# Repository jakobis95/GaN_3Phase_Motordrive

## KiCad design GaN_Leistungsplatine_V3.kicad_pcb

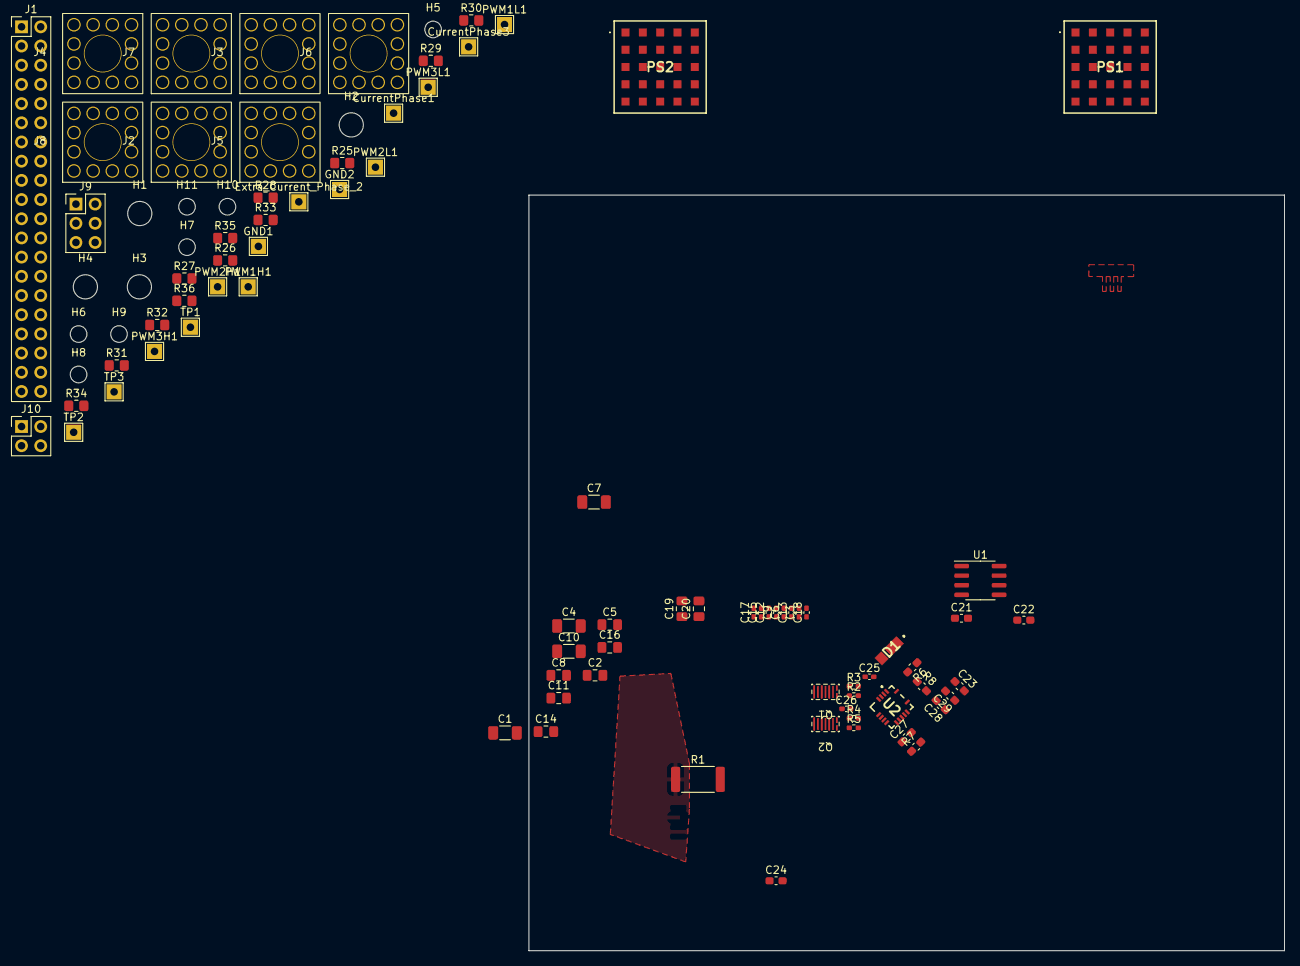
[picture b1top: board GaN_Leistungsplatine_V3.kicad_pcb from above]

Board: 4 copper layers, 100.0 x 100.0 mm, 91 parts (0 on the bottom side), 45 nets, no tracks yet.

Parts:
C1, C4, C7, C10: 4.7u; C_1206_3216Metric_Pad1.33x1.80mm_HandSolder
C2, C5, C8, C11, C14, C16, C19, C20: 1u; C_0805_2012Metric_Pad1.18x1.45mm_HandSolder
C3, C6, C9, C12, C13, C15, C17, C18: 0.1u; C_0402_1005Metric_Pad0.74x0.62mm_HandSolder
C21, C22, C23: 0,1u; C_0603_1608Metric_Pad1.08x0.95mm_HandSolder
C24: 1,2nF; C_0603_1608Metric_Pad1.08x0.95mm_HandSolder
C25, C26: 1,2nF; C_0402_1005Metric_Pad0.74x0.62mm_HandSolder
C27, C29: 100nF; C_0603_1608Metric_Pad1.08x0.95mm_HandSolder
C28: 10nF; C_0603_1608Metric_Pad1.08x0.95mm_HandSolder
CurrentPhase1, CurrentPhase3: TestPoint; TestPoint_THTPad_2.0x2.0mm_Drill1.0mm
D1: DIODE; S110FP
Extra_Current_Phase_2: TestPoint; TestPoint_THTPad_2.0x2.0mm_Drill1.0mm
GND1, GND2: TestPoint; TestPoint_THTPad_2.0x2.0mm_Drill1.0mm
H1, H2, H3, H4: MountingHole; MountingHole_3.2mm_M3_DIN965
H5, H6, H7, H8, H9, H10, H11: MountingHole; MountingHole_2.2mm_M2_DIN965
J1: GPI0_1; PinHeader_2x20_P2.54mm_Vertical
J2, J3, J4, J5, J6, J7, J8: 105-1102-001; TerminalBlock_Wuerth_7461086
J9: Conn_02x03_Counter_Clockwise; PinHeader_2x03_P2.54mm_Vertical
J10: Conn_02x02_Top_Bottom; PinHeader_2x02_P2.54mm_Vertical
PS1: RPMH12-0.5; RPMH1205
PS2: RPM5.0-1.0-CT; RPM5010CT
PWM1H1, PWM1L1, PWM2H1, PWM2L1, PWM3H1, PWM3L1: TestPoint; TestPoint_THTPad_2.0x2.0mm_Drill1.0mm
Q1, Q2: GaN_FET_with_Source_Kelvin_Pin; EPC2065 3.5x1.95 with Kelvin Gate
R1: 7m; R_2512_6332Metric
R2, R4: 6; R_0402_1005Metric_Pad0.72x0.64mm_HandSolder
R3, R5: 3.3; R_0402_1005Metric_Pad0.72x0.64mm_HandSolder
R6: 10; C_0603_1608Metric_Pad1.08x0.95mm_HandSolder
R7: 0; C_0603_1608Metric_Pad1.08x0.95mm_HandSolder
R8: 1000; C_0603_1608Metric_Pad1.08x0.95mm_HandSolder
R25, R27, R29, R31, R33, R35: 3.3; R_0805_2012Metric_Pad1.20x1.40mm_HandSolder
R26, R28, R30, R32, R34, R36: 5.6; R_0805_2012Metric_Pad1.20x1.40mm_HandSolder
TP1: Phase3; TestPoint_THTPad_2.0x2.0mm_Drill1.0mm
TP2: Phase1; TestPoint_THTPad_2.0x2.0mm_Drill1.0mm
TP3: Phase2; TestPoint_THTPad_2.0x2.0mm_Drill1.0mm
U1: LT1999; SOIC-8_3.9x4.9mm_P1.27mm
U2: NCP51810; NCP51810AMNTWG

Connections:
5V: J2.1, J10.2, PS2.A5 (VOUT_1), PS2.B5 (VOUT_2), PS2.C5 (SENSE)
12V: J6.1, J10.1, PS1.A5 (VOUT_1), PS1.B5 (VOUT_2), PS1.C5 (SENSE), PS2.A1 (VIN_1), PS2.A2 (VIN_2)
/DCDC5V/TRIM_2: PS2.E1 (SEQ), PS2.E5 (TRIM)
/DCDC12/PGOOD_1: PS1.D1 (PGOOD), PS2.C1 (CTRL)
/halfbridge1/5V: C21.1, C22.1, U1.1 (V+), U1.4 (V+)
/halfbridge1/12V: C29.2, R6.2, R8.1, U2.14 (VDD)
/halfbridge1/Batt+: C1.1, C2.1, C3.1, C4.1, C5.1, C6.1, C7.1, C8.1, C9.1, C10.1, C11.1, C12.1, C13.1, C14.1, C15.1, C16.1, C17.1, C18.1, C19.1, C20.1, Q1.4 (D)
/halfbridge1/EN_uC: C28.2, R8.2, U2.13 (EN)
/halfbridge1/Phase: R1.1, U1.2 (+IN)
Batt+: J7.1, PS1.A1 (VIN_1), PS1.A2 (VIN_2), PS1.C1 (CTRL)
CurrentPhase1: CurrentPhase1.1, J1.16, J1.28, R27.2, R28.1
CurrentPhase3: CurrentPhase3.1, J1.29, J1.39, R25.2, R26.1
GNDPWR: C1.2, C2.2, C3.2, C4.2, C5.2, C6.2, C7.2, C8.2, C9.2, C10.2, C11.2, C12.2, C13.2, C14.2, C15.2, C16.2, C17.2, C18.2, C19.2, C20.2, C21.2, C23.2, C26.2, C27.2, C28.1, C29.1, GND1.1, GND2.1, J1.12, J1.30, J8.1, J9.2, J9.3, PS1.A3 (GND_1), PS1.A4 (GND_2), PS1.B1 (GND_3), PS1.B2 (GND_4), PS1.B3 (GND_5), PS1.B4 (GND_6), PS1.C2 (GND_7), PS1.C3 (GND_8), PS1.C4 (GND_9), PS1.D2 (GND_10), PS1.D3 (GND_11), PS1.D4 (GND_12), PS1.D5 (GND_13), PS1.E3 (GND_14), PS1.E4 (GND_15), PS2.A3 (GND_1), PS2.A4 (GND_2), PS2.B1 (GND_3), PS2.B2 (GND_4), PS2.B3 (GND_5), PS2.B4 (GND_6), PS2.C2 (GND_7), PS2.C3 (GND_8), PS2.C4 (GND_9), PS2.D2 (GND_10), PS2.D3 (GND_11), PS2.D4 (GND_12), PS2.D5 (GND_13), PS2.E3 (GND_14), PS2.E4 (GND_15), Q2.1 (S), Q2.2 (SS), R7.2, R28.2, R30.2, R32.2, R34.2, R36.2, U1.5 (GND), U2.8 (PGND), U2.10 (SGND)
Hall_A: J1.32, R31.2, R32.1
Hall_B: J1.33, R33.2, R34.1
Hall_C: J1.34, R35.2, R36.1
unnamed: C22.2, U1.8 (SHDN)
unnamed: C23.1, U1.6 (REF)
unnamed: C24.1, C25.1, Q1.2 (SS), U2.4 (SW)
unnamed: C24.2, D1.2 (A), U2.15 (VBEST)
unnamed: C25.2, U2.1 (VDDH)
unnamed: C26.1, U2.5 (VDDL)
unnamed: C27.1, R7.1, U2.9 (DT)
unnamed: D1.1 (K), R6.1
unnamed: J9.4, R31.1
unnamed: J9.5, R33.1
unnamed: J9.6, R35.1
unnamed: J9.1, J10.3, J10.4
unnamed: Q1.1 (S), Q2.4 (D), R1.2, U1.3 (-IN)
unnamed: Q1.3 (G), R2.1, R3.1
unnamed: Q2.3 (G), R4.1, R5.1
unnamed: R2.2, U2.2 (HOSRC)
unnamed: R3.2, U2.3 (HOSNK)
unnamed: R4.2, U2.6 (LOSRC)
unnamed: R5.2, U2.7 (LOSNK)
PWM1H: J1.18, PWM1H1.1
PWM1L: J1.17, PWM1L1.1
PWM2H: J1.20, PWM2H1.1
PWM2L: J1.19, PWM2L1.1
PWM3H: J1.22, PWM3H1.1
PWM3L: J1.21, PWM3L1.1
Phase1: J5.1, TP2.1
Phase2: J4.1, TP3.1
Phase3: J3.1, TP1.1
extraCurrentPhase2: Extra_Current_Phase_2.1, J1.9, J1.23, R29.2, R30.1

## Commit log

2023-01-27 Erster Commit
2023-01-27 hello
2023-01-27 platinen change
